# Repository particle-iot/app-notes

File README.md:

# Application Notes

*Technical application notes for hardware and software designs and best-practices.*

Application notes have been moved and can now be found here:

[https://docs.particle.io/datasheets/app-notes/application-notes/](https://docs.particle.io/datasheets/app-notes/application-notes/)

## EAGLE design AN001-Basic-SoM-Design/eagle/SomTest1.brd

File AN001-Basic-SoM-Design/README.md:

# AN001 - Basic SoM Design

This application note is a simple SoM base board. Like a Boron it can be powered by LiPo battery, USB, or an external DC supply. It includes:

- RGB LED
- bq24195 PMIC
- MAX17043 Fuel Gauge
- USB Connector
- LiPo Connector (JST-PH)
- M.2 SoM Connector

This is the basic set of features you'll probably want to include in a LiPo battery-powered design. The Evaluation Board is also a good reference to use. This design, however, is simple enough that it can be hand-assembled, though you still need a reflow oven and some of the parts (in particular the fuel gauge and PMIC) are tiny and there are a lot of them. 

This board a two-layer circuit board so it can be manufactured inexpensively and edited using the free version of Eagle CAD.

As this board doesn't really do much, you'll unlikely use it as-is, but you can use it as a tutorial for how to hook up the PMIC and fuel gauge.

There is another design in the [SoM first board tutorial](https://docs.particle.io/tutorials/hardware-projects/som-first-board/) that includes additional information that will be useful for building your first board.

The files for this application note can be found in the [Github repository](https://github.com/particle-iot/app-notes/tree/master/AN001-Basic-SoM-Design) for this project.

Author: Rick

## Board

1. bq24195 PMIC
2. XCL223 3.3V regulator
3. M.2 SoM connector
4. RGB LED, reset, and mode buttons
5. Micro USB connector
6. JST-PH battery connector
7. External power input (3.9V - 12V)
8. Charging LED
9. MAX17043 fuel gauge

While the pictures show a simple M3 screw and nut to hold down the SoM, the Eagle files have been updated with a proper standoff assembly. This is described in detail [here](https://docs.particle.io/tutorials/hardware-projects/som-first-board/#hold-down-screw).

## Schematic

This is the M.2 connector, RGB LED, RESET and MODE buttons, and USB connector.

The bq24195 PMIC circuit. You can use a different PMIC, however you'll need to manage its settings yourself as Device OS can only configure this PMIC automatically. If this PMIC is not present, then it will assume you're managing your own PMIC, or you do not have one. For example, a device powered only by USB or disposable batteries would not need a PMIC.

The XCL223 3.3V regulator. This regulator is required when using 3.7V LiPo batteries because they can have a voltage as high as 4.2V during charging. With some other types of batteries that never exceed 3.6V at any time, you can omit this regulator as the nRF52840 can be used at up to 3.6V on the 3V3 pin.

The MAX17043 fuel gauge. You can use a different fuel gauge, however as of Device OS 1.3.1, you cannot hook an alternate fuel gauge into the system so the battery reports correctly with device diagnostics. This is planned for the future.

## BOM

The bill of materials for this board is:

| Quan | Part | Example | Price | 
| :---: | --- | --- | ---: |
| 1 | 150Ω resistor 0603 | [Panasonic ERJ-3EKF1500V](https://www.digikey.com/product-detail/en/panasonic-electronic-components/ERJ-3EKF1500V/P150HCT-ND/198177) | | 
| 1 | 332Ω resistor 0603 | [Panasonic ERJ-3EKF3320V](https://www.digikey.com/product-detail/en/panasonic-electronic-components/ERJ-3EKF3320V/P332HCT-ND/198336) | | 
| 5 | 1K resistor 0603 | [Panasonic ERJ-PB3D1001V](https://www.digikey.com/product-detail/en/panasonic-electronic-components/ERJ-PB3D1001V/P20283CT-ND/6214538) | | 
| 2 | 4.7K resistor 0603 | [Panasonic ERJ-PA3J472V](https://www.digikey.com/product-detail/en/panasonic-electronic-components/ERJ-PA3J472V/P4.7KBZCT-ND/5036332) | | 
| 1 | 5.6K resistor 0603 | [Panasonic ERJ-3EKF5601V](https://www.digikey.com/product-detail/en/panasonic-electronic-components/ERJ-3EKF5601V/P5.60KHCT-ND/1746792) | | 
| 5 | 10K resistor 0603 | [Panasonic ERJ-PA3J103V](https://www.digikey.com/product-detail/en/panasonic-electronic-components/ERJ-PA3J103V/P10KBZCT-ND/5036237) | |
| 1 | 0.001 uF capacitor 0603 | [Murata GRM1885C1H102JA01D](https://www.digikey.com/product-detail/en/murata-electronics-north-america/GRM1885C1H102JA01D/490-1451-1-ND/587655) | | 
| 1 | 0.047 uF capacitor 0603 | [Murata GCJ188R71H473KA12D](https://www.digikey.com/product-detail/en/murata-electronics-north-america/GCJ188R71H473KA12D/490-5854-1-ND/2785840) | | 
| 1 | 0.01 uF capacitor 0603 | [Murata GCM188R72A103KA37J](https://www.digikey.com/product-detail/en/murata-electronics-north-america/GCM188R72A103KA37J/490-8028-1-ND/4380313) | | 
| 2 | 1 uF capacitor 0603 | [Samsung CL10B105KA8NNNC](https://www.digikey.com/product-detail/en/samsung-electro-mechanics-america-inc/CL10B105KA8NNNC/1276-1184-1-ND/3889270) | | 
| 2 | 4.7 uF capacitor 0603 | [Murata GRM188R60J475KE19J](https://www.digikey.com/product-detail/en/murata-electronics-north-america/GRM188R60J475KE19J/490-6407-1-ND/3845604) | | 
| 7 | 10 uF capacitor 0805 | [Murata GRM21BR61C106KE15L](https://www.digikey.com/product-detail/en/murata-electronics-north-america/GRM21BR61C106KE15L/490-3886-1-ND/965928) | | 
| 1 | 2.2 uH inductor 1008 | [Bourns SRN2512-2R2M/](https://www.digikey.com/product-detail/en/bourns-inc/SRN2512-2R2M/SRN2512-2R2MCT-ND/4867759) | $0.31 | 
| 1 | RS1JFP Diode | [On Semiconductor RS1JFP](https://www.digikey.com/product-detail/en/on-semiconductor/RS1JFP/RS1JFPCT-ND/5722970) | $0.44 | 
| 1 | MAX17043 FuelGauge | [MAX17043X+T10](https://www.mouser.com/ProductDetail/Maxim-Integrated/MAX17043X%2bT10?qs=sGAEpiMZZMtKiEBa%2FXu9%252BOav9R4qKwGZ) | $3.09|
| 1 | bq24195 PMIC | [Texas Instruments BQ24195LRGER](https://www.digikey.com/product-detail/en/texas-instruments/BQ24195LRGER/296-49149-1-ND/9351369)| $2.93 | 
| 1 | XCL223 3.3V Regulator | [Torex XCL223A333D2-G](https://www.digikey.com/product-detail/en/torex-semiconductor-ltd/XCL223A333D2-G/893-1416-1-ND/8256118) | $2.63 |
| 2 | 4.5mm tactile switch | [E-Switch TL3305AF160QG](https://www.digikey.com/product-detail/en/e-switch/TL3305AF160QG/EG5350CT-ND/5816195) | $0.20 |
| 1 | USB micro B connector | [Amphenol FCI 10118194-0001LF](https://www.digikey.com/products/en?keywords=609-4618-1-nd) | $0.42 | 
| 1 | JST-PH battery connector | [JST B2B-PH-K-S(LF)(SN)](https://www.digikey.com/product-detail/en/jst-sales-america-inc/B2B-PH-K-S-LF-SN/455-1704-ND/926611) | $0.17 | 
| 1 | RGB LED 4PLCC | [Cree CLMVC-FKA-CL1D1L71BB7C3C3](https://www.digikey.com/product-detail/en/cree-inc/CLMVC-FKA-CL1D1L71BB7C3C3/CLMVC-FKA-CL1D1L71BB7C3C3CT-ND/9094273 CLMVC-FKA-CL1D1L71BB7C3C3) | $0.19 |
| 1 | Red LED 0603 5mA | [Lite-On LTST-C193KRKT-5A](https://www.digikey.com/product-detail/en/lite-on-inc/LTST-C193KRKT-5A/160-1830-1-ND/2356251) | $0.41 |
| 1 | M.2 connector | [TE Connectivity 2199230-4](https://www.digikey.com/product-detail/en/te-connectivity-amp-connectors/2199230-4/A115904CT-ND/4208916) | $1.42 |
| 1 | M.2 standoff | [JAE 	SM3ZS067U410-NUT1-R1200](https://www.digikey.com/product-detail/en/jae-electronics/SM3ZS067U410-NUT1-R1200/670-2865-1-ND/5955849) | $1.25 |
| 1 | M2*3 screw w/4mm head | [example](https://www.amazon.com/gp/product/B07NZ32TRB/ref=ppx_yo_dt_b_asin_title_o00_s00) | |

## Eagle Files

The eagle directory contains files for Autodesk Eagle CAD 9. It is a small two-layer board you can view and edit it with the free version of Eagle CAD.

- SomTest1.sch - Schematic
- SomTest1.brd - Board File
- SomTest1v4.zip - Gerbers
- SomTest1.lbr - Library file containing all of the components on this board
- SomTest1-brd.pdf - PDF version of the board
- SomTest1-sch.pdf - PDF version of the schematic

The Gerber files were tested at JLCPCB but were created using the default Eagle CAD settings so they should work with many fabrication houses.

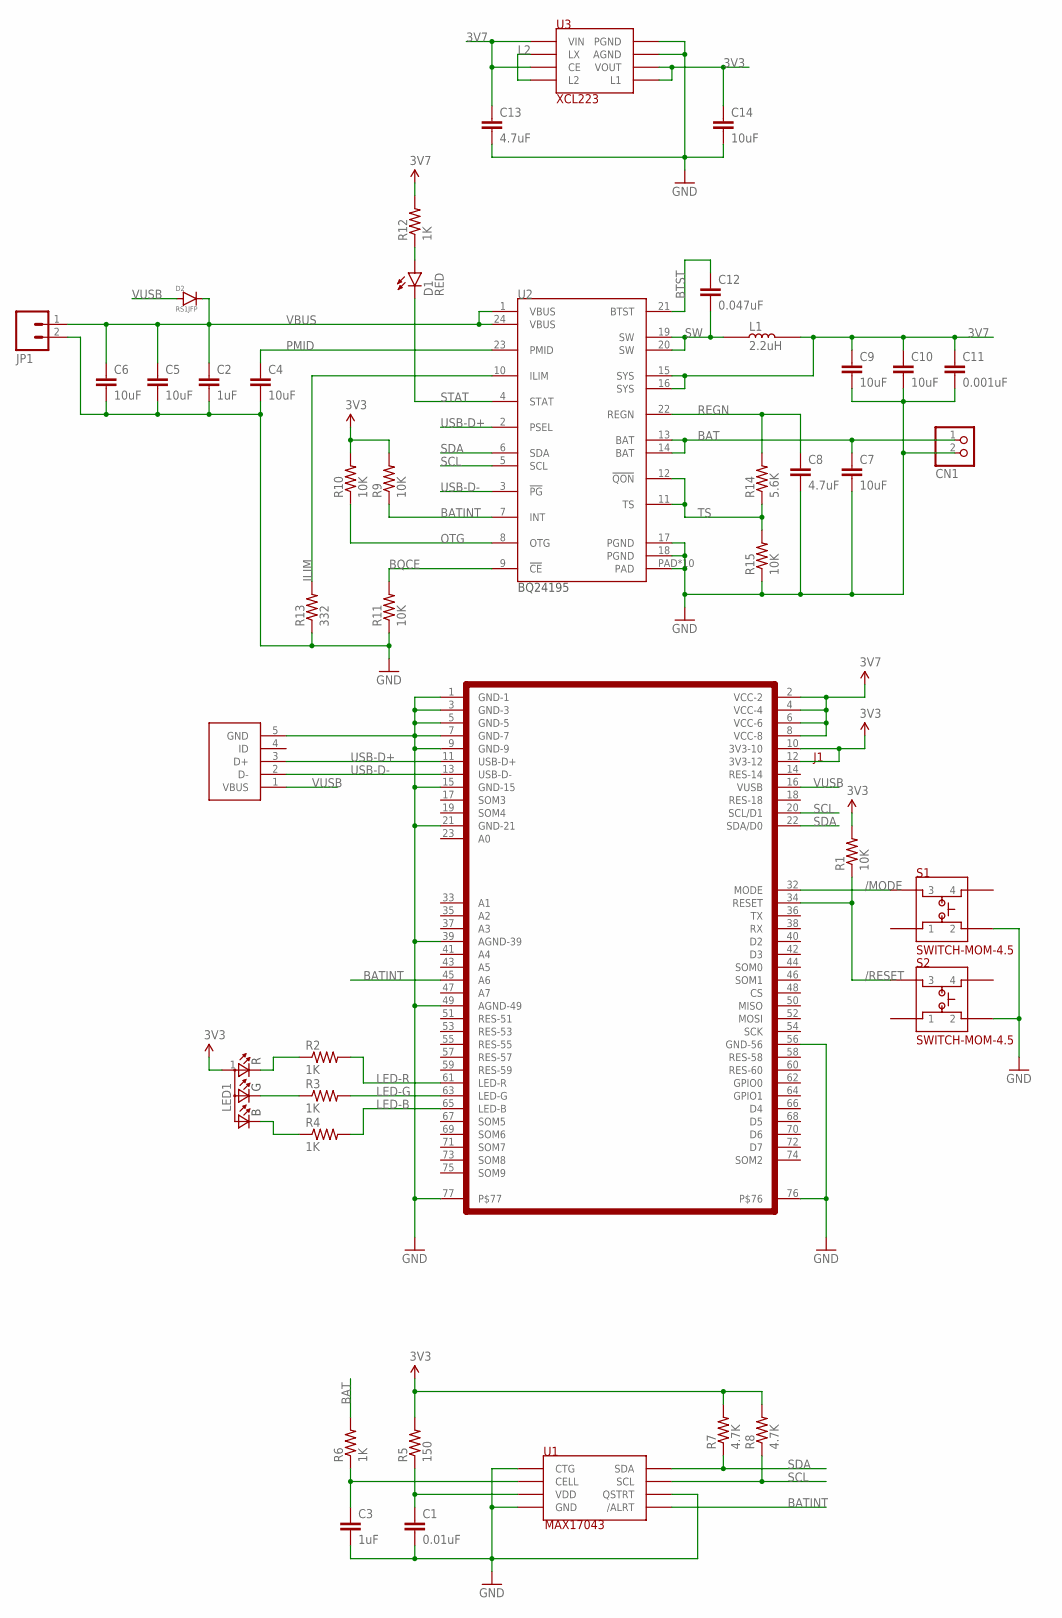
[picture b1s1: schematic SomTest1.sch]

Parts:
C1: 0.01uF; 0603-CAP
C2, C3: 1uF; 0603-CAP
C4, C5, C6, C7, C9, C10, C14: 10uF; 0603-CAP
C8, C13: 4.7uF; 0603-CAP
C11: 0.001uF; 0603-CAP
C12: 0.047uF; 0603-CAP
CN1: JST_2PIN-THM; JST-PH-2-THM
D1: RED; LED-0603
D2: RS1JFP; SOD-123HE-ON
J1: SPARK_M.2EKEY; SPARK_M.2EKEY-LESS-CREAM
JP1: M02PTH; 1X02
L1: 2.2uH; 1008-BOURNS
LED1: LED-RGB-CREE-SMD
R1, R9, R10, R11, R15: 10K; 0603-RES
R2, R3, R4, R6, R12: 1K; 0603-RES
R5: 150; 0603-RES
R7, R8: 4.7K; 0603-RES
R13: 332; 0603-RES
R14: 5.6K; 0603-RES
S1, S2: SWITCH-MOM-4.5
U1: MAX17043; 9UCSP-MAXIM
U2: BQ24195; 24VFQN-TI
U3: XCL223; REG-XCL223-LESS-CREAM
U$3: USB-MICRO-B-SOCKET-AMPHENOL; USB-B-SMT-AMPHENOL

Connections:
3V3: C14.1, J1.10 (3V3-10), J1.12 (3V3-12), LED1.1 (A), R1.2, R5.2, R7.2, R8.2, R9.2, R10.2, U3.3 (VOUT), U3.7 (L1)
3V7: C9.1, C10.1, C11.1, C13.1, J1.2 (VCC-2), J1.4 (VCC-4), J1.6 (VCC-6), J1.8 (VCC-8), L1.2, R12.2, U2.15 (SYS), U2.16 (SYS), U3.4 (CE), U3.6 (VIN)
/MODE: J1.32 (MODE), S1.3
/RESET: J1.34 (RESET), R1.1, S2.3
BAT: C7.1, CN1.1 (2), R6.2, U2.13 (BAT), U2.14 (BAT)
BATINT: J1.45 (A6), R9.1, U1.C1 (/ALRT), U2.7 (INT)
BQCE: R11.2, U2.9 (!CE)
BTST: C12.1, U2.21 (BTST)
GND: C1.2, C2.2, C3.2, C4.2, C5.2, C6.2, C7.2, C8.2, C9.2, C10.2, C11.2, C13.2, C14.2, CN1.2 (1), J1.1 (GND-1), J1.3 (GND-3), J1.5 (GND-5), J1.7 (GND-7), J1.9 (GND-9), J1.15 (GND-15), J1.21 (GND-21), J1.39 (AGND-39), J1.49 (AGND-49), J1.56 (GND-56), J1.76, J1.77, JP1.2, R11.1, R13.1, R15.1, S1.2, S2.2, U1.A3 (CTG), U1.B1 (QSTRT), U1.C3 (GND), U2.17 (PGND), U2.18 (PGND), U2.PAD, U2.PAD@1 (PAD), U2.PAD@2 (PAD), U2.PAD@3 (PAD), U2.PAD@4 (PAD), U2.PAD@5 (PAD), U2.PAD@6 (PAD), U2.PAD@7 (PAD), U2.PAD@8 (PAD), U2.PAD@9 (PAD), U3.1 (PGND), U3.2 (AGND), U$3.5 (GND)
ILIM: R13.2, U2.10 (ILIM)
L2: U3.5 (LX), U3.8 (L2)
LED-B: J1.65 (LED-B), R4.2
LED-G: J1.63 (LED-G), R3.2
LED-R: J1.61 (LED-R), R2.2
unnamed: LED1.3 (G), R3.1
unnamed: C3.1, R6.1, U1.B3 (CELL)
unnamed: C1.1, R5.1, U1.C2 (VDD)
unnamed: LED1.4 (R), R2.1
unnamed: D1.A, R12.1
unnamed: LED1.2 (B), R4.1
OTG: R10.1, U2.8 (OTG)
PMID: C4.1, U2.23 (PMID)
REGN: C8.1, R14.2, U2.22 (REGN)
SCL: J1.20 (SCL/D1), R8.1, U1.A2 (SCL), U2.5 (SCL)
SDA: J1.22 (SDA/D0), R7.1, U1.A1 (SDA), U2.6 (SDA)
STAT: D1.C, U2.4 (STAT)
SW: C12.2, L1.1, U2.19 (SW), U2.20 (SW)
TS: R14.1, R15.2, U2.11 (TS), U2.12 (!QON)
USB-D+: J1.11 (USB-D+), U2.2 (PSEL), U$3.3 (D+)
USB-D-: J1.13 (USB-D-), U2.3 (!PG), U$3.2 (D-)
VBUS: C2.1, C5.1, C6.1, D2.1 (CATHODE), JP1.1, U2.1 (VBUS), U2.24 (VBUS)
VUSB: D2.2 (ANODE), J1.16 (VUSB), U$3.1 (VBUS)

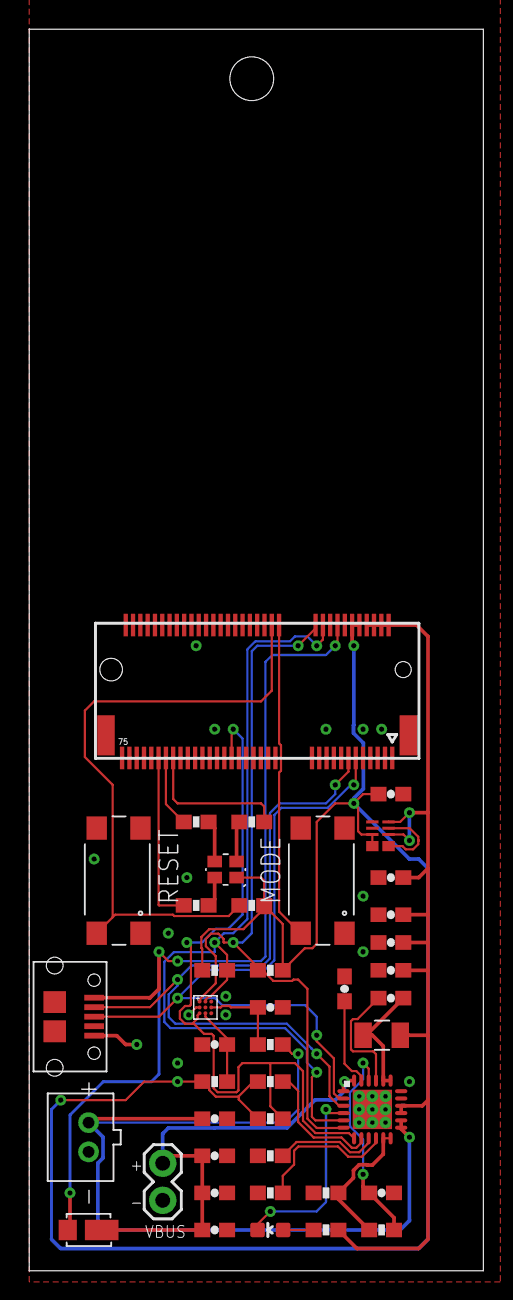
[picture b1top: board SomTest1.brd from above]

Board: 2 copper layers, 31.1 x 85.0 mm, 42 parts (0 on the bottom side), 32 nets.

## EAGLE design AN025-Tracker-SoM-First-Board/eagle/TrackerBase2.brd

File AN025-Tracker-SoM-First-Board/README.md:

# AN025 Tracker SoM First Board

This tutorial shows how to make a simple base board for the Tracker SoM that has a number of features from the Tracker Carrier Board (used in the Tracker One), however can easily be modified to fit your needs. 

The full tutorial can be found in [the documentation](https://docs.particle.io/tutorials/asset-tracking/tracker-som-first-board/). 

The Eagle CAD files can be found in the [Github repository](https://github.com/particle-iot/app-notes/tree/master/AN025-Tracker-SoM-First-Board) for this project.

Standard features:

- SETUP and MODE buttons
- RGB status LED
- Charge LED
- MCU USB connector
- NFC antenna connector

Features from the Tracker Carrier Board/Tracker One (all are optional):

- GNSS LED
- Thermistor
- USER button
- B8B-PH connector for connecting to an M8 connector
- 10-pin SWD/JTAG debug connector
- SPI FRAM

Other features:

- CAN termination enable jumper
- Ability to add a mezzanine card for expansion including all ports, GPIO, CAN, and power options
- Optional GNSS/RTC backup battery (CR1220) with DIP switch to enable/disable
- GNSS and cellular USB connectors (optional)
- Fits in an off-the-shelf IP67 weather-resistant enclosure
- Simple two-layer board is inexpensive to fabricate and can be developed in the free version of Eagle CAD

Author: Rick

## Board Diagram

| Item | Description |
| ---: | :--- |
|  1 | SWD/JTAG 10-pin debug connector |
|  2 | NFC Antenna U.FL |
|  3 | USER button (A1) |
|  4 | RGB Status LED |
|  5 | RESET button |
|  6 | GNSS LED, blue (A2) |
|  7 | MODE button |
|  8 | Charge LED, orange |
|  9 | GNSS/RTC battery, CR1220 |
| 10 | LiPo battery connector, JST-PH |
| 11 | VIN Power Input, 3.9 - 17 VDC |
| 12 | GNSS/RTC battery switch |
| 13 | Trace jumpers for A0, A1, A2 |
| 14 | CAN Termination jumper (0.1") |
| 15 | B8B-PH connector to M8 connector |
| 16 | MCU USB (Micro B) | 
| 17 | Expansion Connector Left |
| 18 | Expansion Connector Right |
| 19 | GNSS USB (Micro B) |
| 20 | SPI FRAM |
| 21 | Cellular USB (Micro B) |
| 22 | Thermistor |
| 23 | Tracker SoM |

In enclosure:

With mezzanine expansion board installed:

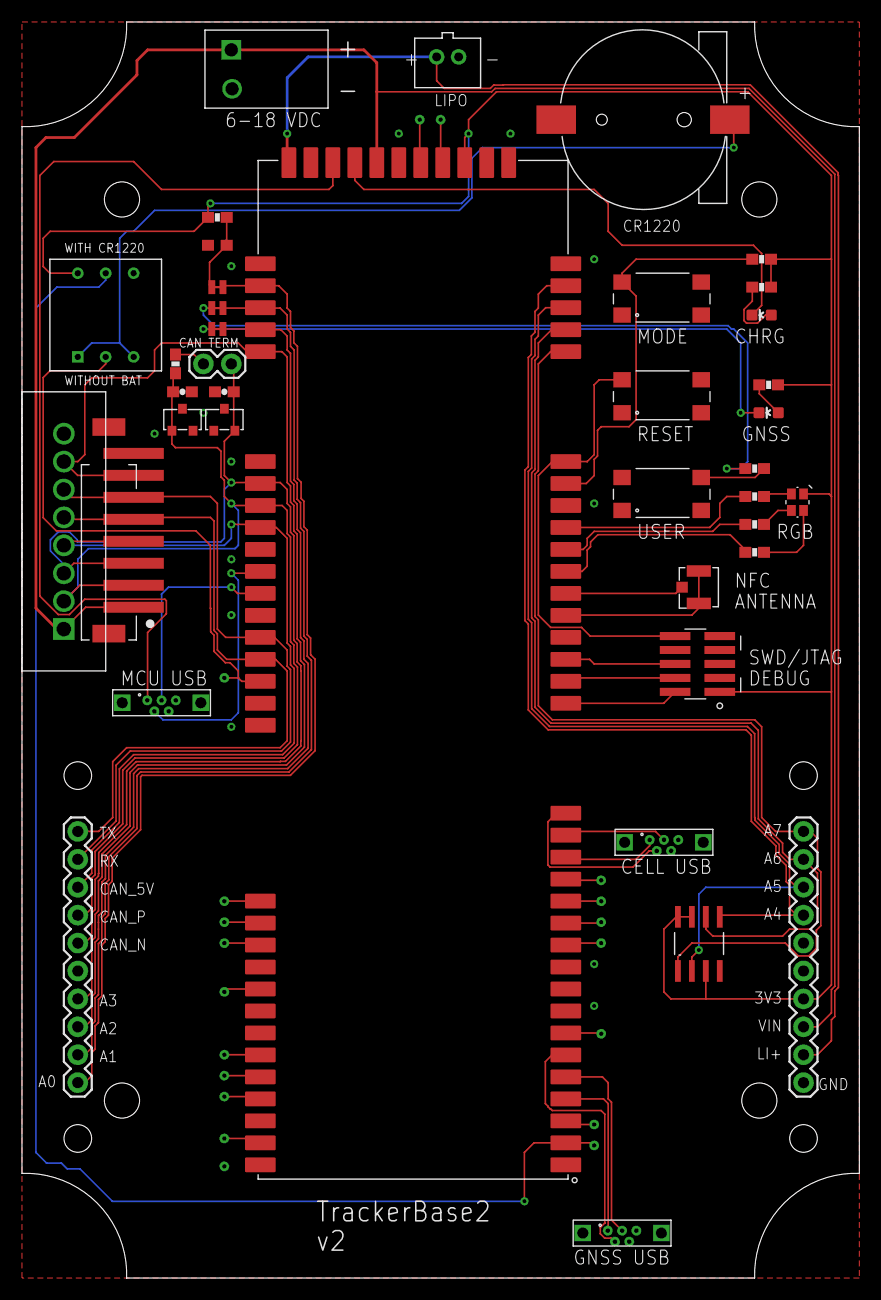
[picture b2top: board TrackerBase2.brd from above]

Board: 2 copper layers, 76.2 x 114.3 mm, 58 parts (0 on the bottom side), 66 nets.

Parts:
C1, C2: 47pF; 0603-CAP
CN1: JST-PH-2-THM
D1: ORANGE; LED-0603
D2: BLUE; LED-0603
D3, D4: MMBZ27VCLT1G; SOT-23-3-ON
J1, J4, J7: USB-MICRO-B-VERT-PTH
J2: U.FL; CONN-UFL-TE
J3: JTAG-MICRO-2X5
J5: CONN-B8B-M8; JST_B8B-PH-SM4-TB(LF)(SN)
J6: TERMBLOCK-8X0.1
J8: TERMBLOCK-2X3.5MM-45
JP1, JP2: M10; 1X10
JP3: M02PTH; 1X02
LED1: RGB; LED-RGB-CREE-SMD
R1, R2, R3: 1K; 0603-RES
R4: 10K; 0603-RES
R5: 270; 0603-RES
R6, R10: 100; 0603-RES
R7: 120; 0603-RES
R8: 100K; 0603
R9: 100K; 0603-RES
S1, S2, S3: SWITCH-MOM-4.5
S4: SWITCH-DIP-DPDT
SJ1, SJ2, SJ3: JUMPER-PAD-2-NC_BY_TRACENO_SILK; PAD-JUMPER-2-NC_BY_TRACE_NO_SILK
TP1, TP2, TP3, TP4, TP5, TP6, TP7, TP8, TP9, TP10, TP11, TP12, TP13, TP14, TP15, TP16, TP17, TP18, TP19: TEST-POINTTP_15TH_THRU; TP_15TH
U1: TRACKER-SOM-SKIP-NC
U2: MB85RS256; 8-SOIC-MAXIM
U$4: CR1220-KEYSTONE

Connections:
3V3: J3.1, JP1.4, LED1.1, R4.2, R5.2, R6.2, R9.2, S4.C1-2, U1.45, U2.3, U2.7, U2.8
A0: JP2.10, SJ1.2, U1.55
A1: JP2.9, SJ2.2, U1.56
A2: JP2.8, SJ3.2, U1.57
A3: J5.7, J6.P$7, JP2.7, U1.58
A4: JP1.7, U1.41, U2.5
A5: JP1.8, U1.40, U2.2
A6: JP1.9, U1.39, U2.6
A7: JP1.10, U1.38, U2.1
BAT+: S4.C1-1, S4.C2-1, U$4.POS
BLUE: R3.1, U1.28
CAN_5V: J5.4, J6.P$4, JP2.3, U1.66
CAN_N: C2.2, D4.2, J5.3, J6.P$3, JP2.5, JP3.1, U1.64
CAN_P: C1.1, D3.1, J5.2, J6.P$2, JP2.4, R7.2, U1.65
CELL_D+: J1.3, U1.16
CELL_D-: J1.2, U1.17
CELL_GPS_RF: TP14.P$1, U1.87
CELL_GPS_RX: TP7.P$1, U1.83
CELL_GPS_TX: TP8.P$1, U1.84
CELL_RI: TP9.P$1, U1.85
CELL_VBUS: J1.1, U1.15
GND: C1.2, C2.1, CN1.2, D3.2, D4.1, J1.5, J3.3, J3.5, J3.9, J4.5, J5.8, J6.P$8, J7.5, J8.2, JP1.1, R8.1, S1.2, S2.2, S3.1, S4.C2-2, TP19.P$1, U1.1, U1.8, U1.10, U1.25, U1.31, U1.42, U1.43, U1.48, U1.52, U1.54, U1.63, U1.67, U1.70, U1.75, U1.86, U1.88, U1.89, U1.93, U1.95, U2.4, U$4.NEG
GNSS_ANT_PWR: TP11.P$1, U1.91
GNSS_BAT: S4.C1, TP17.P$1, U1.2
GNSS_BOOT: TP10.P$1, U1.90
GNSS_LNA_EN: TP12.P$1, U1.92
GNSS_N: J4.2, U1.6
GNSS_P: J4.3, U1.5
GNSS_PULSE: TP5.P$1, U1.7
GNSS_RESET: TP6.P$1, U1.3
GNSS_RF: TP13.P$1, U1.94
GNSS_VBUS: J4.1, U1.4
GREEN: R2.1, U1.29
LI+: CN1.1, JP1.2, U1.53
MCU_D+: J7.3, U1.69
MCU_D-: J7.2, U1.68
MODE: R4.1, S1.3, U1.32
unnamed: JP3.2, R7.1
unnamed: LED1.2, R3.2
unnamed: LED1.3, R2.2
unnamed: LED1.4, R1.2
unnamed: D1.A, R5.1
unnamed: R8.2, R9.1, SJ1.1
unnamed: D2.A, R6.1
unnamed: R10.1, S3.4
unnamed: R10.2, SJ2.1
unnamed: D2.C, SJ3.1
NFC1: J2.PIN, U1.27
NFC2: J2.BL, J2.BR, U1.26
PMID: TP15.P$1, U1.47
RED: R1.1, U1.30
RESET: J3.10, S2.3, U1.33
RTC_BAT: S4.C2, TP18.P$1, U1.73
RX: J5.6, J6.P$6, JP2.2, U1.71
STAT: D1.C, U1.50
SWDCLK: J3.4, U1.23
SWDIO: J3.2, U1.22
SWO: J3.6, U1.24
TS: TP16.P$1, U1.46
TX: J5.5, J6.P$5, JP2.1, U1.72
VBUS: J7.1, U1.51
VIN: J5.1, J6.P$1, J8.1, JP1.3, U1.49
WIFI_BOOT: TP3.P$1, U1.12
WIFI_EN: TP4.P$1, U1.11
WIFI_RXD: TP1.P$1, U1.14
WIFI_TXD: TP2.P$1, U1.13

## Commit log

2019-08-21 AN001 Basic SoM Board
2019-09-17 AN002-Device-Powerdown
2019-09-24 Add AN003 Interpreting Cloud Debug
2019-10-16 Split cloud debug into two notes
2019-10-16 Fix typo
2019-10-24 Update M.2 standoff
2019-11-22 Minor updates
    - Removed unused 0.1uF capactitor from BoM
    - Add missing JST-PH connector
2019-12-11 Add threading explainer
2019-12-11 Fix threading explainer directory name
2019-12-16 AN006 Vehicle Power
    - Vehicle Power Design
2019-12-18 Tower Info
2019-12-18 AN007 Update Links
2020-01-27 AN008
2020-01-27 Fix AN008 label
2020-01-28 Update AN008
2020-01-30 Fix missing program option for resetore device
2020-03-10 Add links to Github repos
2020-04-30 New App Notes
    - AN009 Publish Example Code
    - AN010 About Finite State Machines
2020-04-30 Fix links
2020-06-22 AN011
    - Initial version
2020-06-22 AN011
    - Add links
2020-06-22 Fix typo in AN011
2020-07-17 M8 breakout
2020-07-20 Keypad Tutorial
2020-07-20 CAN bus app note
2020-07-21 Tank Level
2020-07-22 checkpoint
    - Not complete
2020-07-22 Updates for Edge v8
    - Tracker is a singleton now
2020-07-22 Final edits
2020-07-22 Minor edits
2020-08-03 CAN bus
    - Add note about jumper J1 on the simulator
2020-08-05 Update MCP_CAN_RK library version
2020-08-05 AN019 Thermocouple Example
2020-08-06 M8 cable details
2020-08-09 Update M8 voltage
2020-08-10 AN020 and AN021
    - 4-20mA sensor examples
2020-08-11 AN021
    - Change value of sense resistor to 10 ohms
2020-08-13 Update TowerInfo link
2020-08-19 AN022 Tracker SHT3x
2020-08-27 Updater license
2020-09-17 Add SIM denied example
2020-09-17 Update CAN app note
    - Use can-mcp25x library
2020-09-29 Building tracker-edge from source
2020-09-29 AN025 Tracker SoM First Board
2020-09-30 AN024 Tracker Relay
2020-10-01 Fix VIN voltages
2020-10-16 Add solutions accelerator
2020-10-19 Minor updates
    - Add author for each note
    - Add links from top level readme
    - Add link to repository in note (needed when searching from support site)
2020-10-19 Add solutions accelerator (#6)
    * Add solutions accelerator
    * Minor updates
    - Add author for each note
    - Add links from top level readme
    - Add link to repository in note (needed when searching from support site)
2020-10-21 AN023 Watchdog Timers
2020-10-21 Add missing description
2020-11-02 Update tracker device OS versions
2020-11-09 Fix tracker edge instructions
    See: https://github.com/particle-iot/docs/pull/1127/commits/4f97e069f0201a3d1979b56b855dc66f90f1d747
2021-01-05 Update thread mutex example
2021-01-15 Update AN017 CAN
    - Add configuration schema so values can be set
2021-02-01 Add AN027 Tracker Button and LEDs
2021-02-03 AN005 minor correction
2021-02-03 Change CAN bus current
    - Should be 370 mA maximum recommended, not 400 mA
2021-02-10 Add terminating resistor note
2021-03-08 Mark as development device
    - Mention that you must mark tracker devices as development before flashing locally (ch74829)
2021-03-09 Move app notes to docs
